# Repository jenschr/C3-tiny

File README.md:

# ESP32 C3-tiny
A Tiny but very functional DevBoard with Temperature/Moisture sensor and 5 programmable LEDs.

## Why smaller?

The official devboard from Espressif is crazy big for such a tiny module? I wanted to make something that leaves two rows on each side when put into a normal half-size breadboard, while testing out the Espressif ESP32 C3 module. Also - I could make this as a christmas gift for my son since he studies electronics and likes RiscV? And then I could publish it as a starting point for others to design their own boards? Why not!

I won't say that the pinout isn't a bit messy (as not in correct order), but all pins are broken out and this project should make it easy for anyone to create their own Espressif C3 based boards. The repository is complete with [Kicad files](pcb/), [BOM](bom/) and [test code for Arduino](code/).

## Pinout

[*] All the module pins are broken out and some pins such as pin 18 + 19 is used for the USB connection. That means that you cannot connect anything to these if you want to use USB.

[*] You also cannot use pins 6 (SDA) and 7 (SCL) for other things if you want to also use the SHT31 sensor connected to these pins (I2C Bus). Other I2C devices shopuld also be connected to these pins. Note that there are pullup resistors on these pins. If you keep this in mind, you can use the pins if you don't use I2C.

[*] The Boot button may be used as an input - after startup has finished.

## Arduino usage

Select "ESP32C3 Dev Module" as the board and set "USB CDC on Boot" to true. The SHT31 sensor is on address 0x44 and you need to start I2C using pins 6 and 7 like this:

`Wire.begin(6,7);`

The five RGB LEDs are connected to pin 8. Check out the code example for details.

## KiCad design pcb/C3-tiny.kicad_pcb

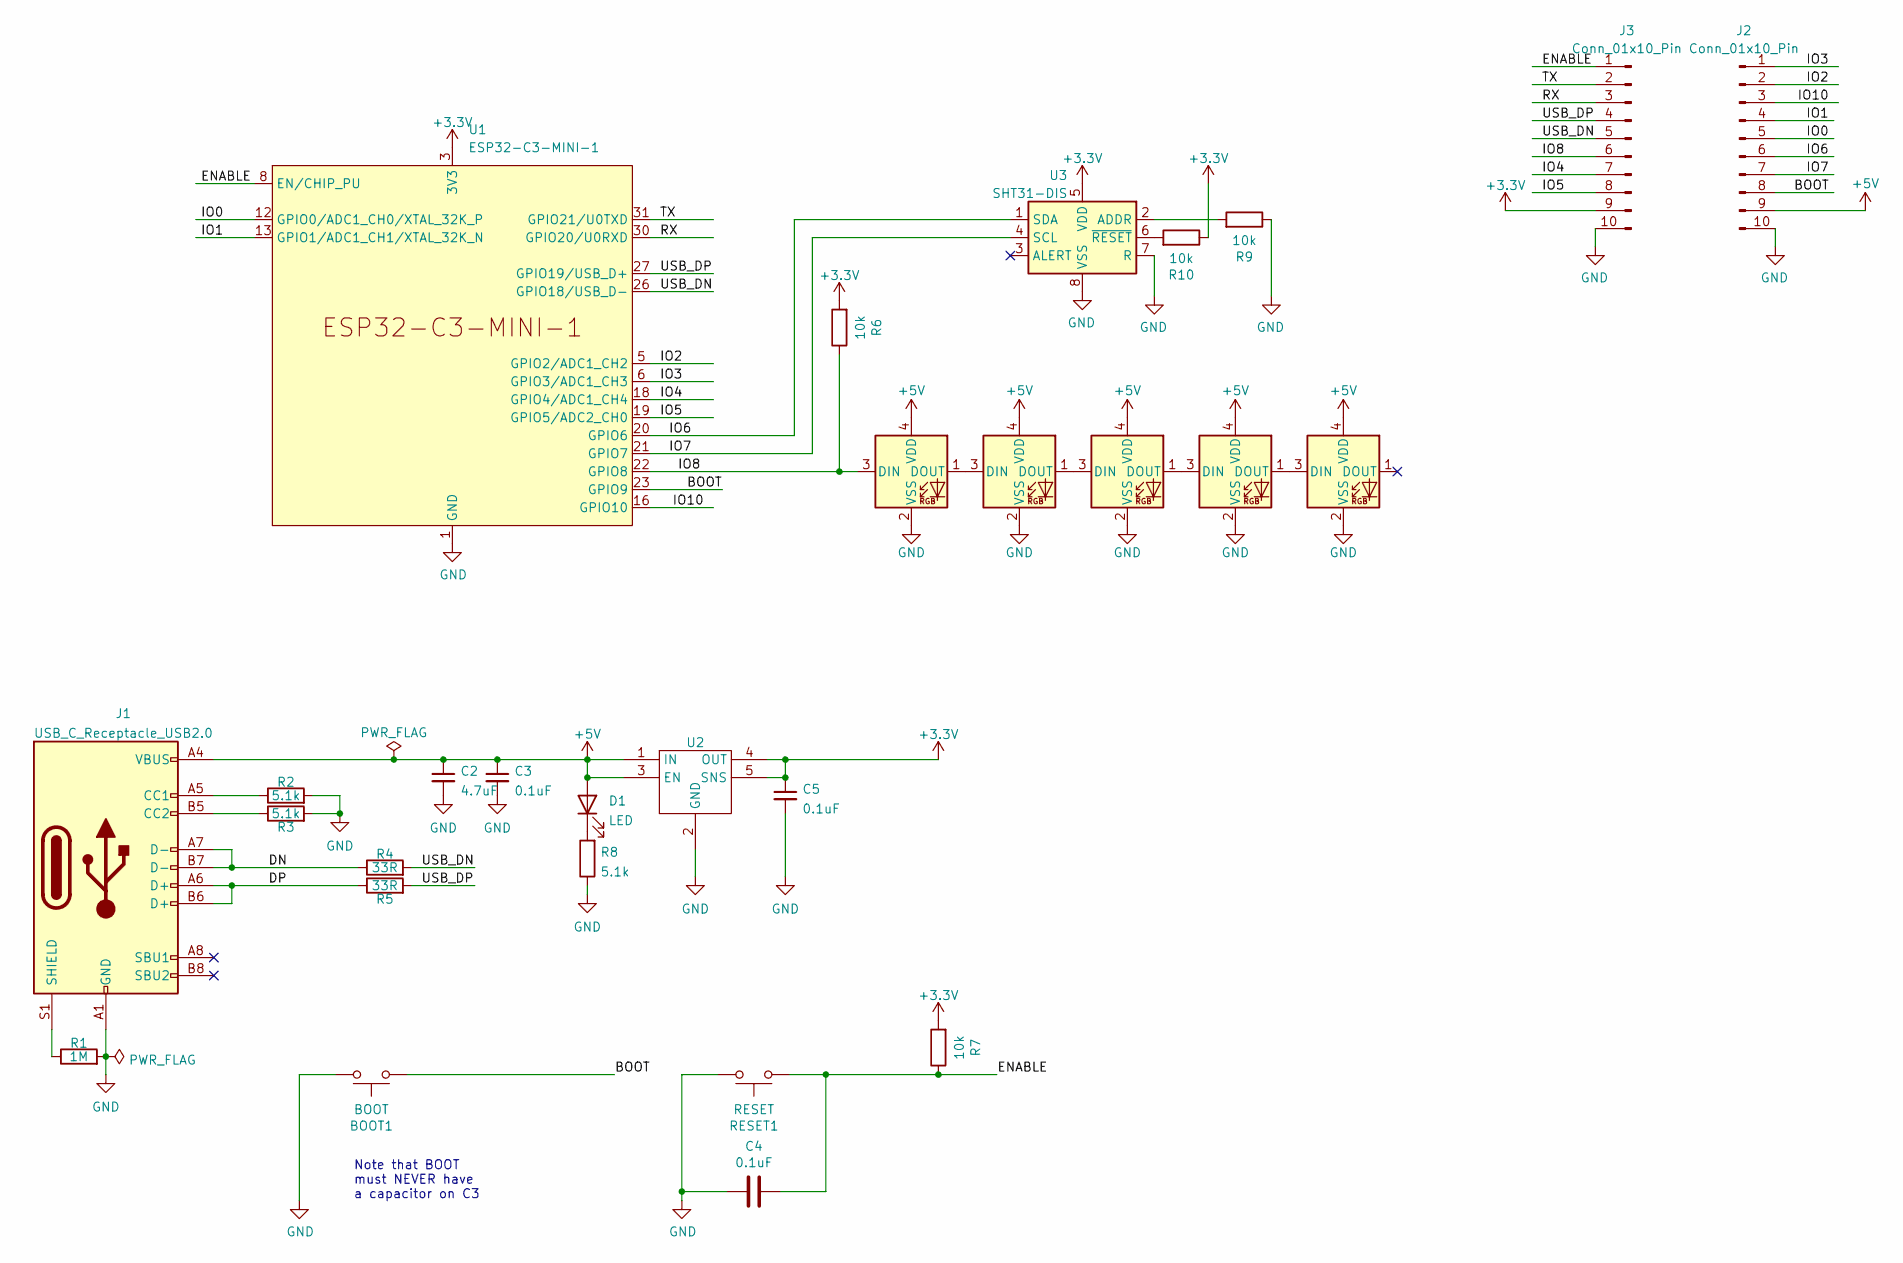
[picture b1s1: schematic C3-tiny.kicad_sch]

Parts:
BOOT1: BOOT; KMR241GLFS; MPN KMR241GLFS
C2: 4.7uF; C_0805_2012Metric
C3, C4, C5: 0.1uF; C_0603_1608Metric_Pad1.08x0.95mm_HandSolder
D1: LED; LED_0603_1608Metric_Pad1.05x0.95mm_HandSolder
J1: USB_C_Receptacle_USB2.0; TYPE-C-31-M-14
J2, J3: Conn_01x10_Pin; PinHeader_1x10_P2.54mm_Vertical
L1, L2, L3, L4, L5: SK6812MINI; LED_SK6812_EC15_1.5x1.5mm
R1: 1M; R_0603_1608Metric_Pad0.98x0.95mm_HandSolder
R2, R3, R8: 5.1k; R_0603_1608Metric
R4, R5: 33R; R_0603_1608Metric
R6, R7, R9, R10: 10k; R_0603_1608Metric; MPN RMCF0603JG10K0
RESET1: RESET; KMR241GLFS; MPN KMR241GLFS
U1: ESP32-C3-MINI-1
U2: NCP692MN33T2G; DFN-6-1EP_3x3mm_P0.95mm_EP1.7x2.6mm
U3: SHT31-DIS; Sensirion_DFN-8-1EP_2.5x2.5mm_P0.5mm_EP1.1x1.7mm; MPN SHT31-DIS

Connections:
+3.3V: C5.1, J3.9, R6.2, R7.2, R10.1, U1.3 (3V3), U2.4 (OUT), U2.5 (SNS), U3.5 (VDD)
+5V: C2.1, C3.1, D1.2 (A), J1.A4 (VBUS), J1.A9 (VBUS), J1.B4 (VBUS), J1.B9 (VBUS), J2.9, L1.4 (VDD), L2.4 (VDD), L3.4 (VDD), L4.4 (VDD), L5.4 (VDD), U2.1 (IN), U2.3 (EN), U2.6 (IN)
/BOOT: BOOT1.1, J2.8, U1.23 (GPIO9)
/DN: J1.A7 (D-), J1.B7 (D-), R4.1
/DP: J1.A6 (D+), J1.B6 (D+), R5.1
/ENABLE: C4.1, J3.1, R7.1, RESET1.1, U1.8 (EN/CHIP_PU)
/IO0: J2.5, U1.12 (GPIO0/ADC1_CH0/XTAL_32K_P)
/IO1: J2.4, U1.13 (GPIO1/ADC1_CH1/XTAL_32K_N)
/IO2: J2.2, U1.5 (GPIO2/ADC1_CH2)
/IO3: J2.1, U1.6 (GPIO3/ADC1_CH3)
/IO4: J3.7, U1.18 (GPIO4/ADC1_CH4)
/IO5: J3.8, U1.19 (GPIO5/ADC2_CH0)
/IO6: J2.6, U1.20 (GPIO6), U3.1 (SDA)
/IO7: J2.7, U1.21 (GPIO7), U3.4 (SCL)
/IO8: J3.6, L1.3 (DIN), R6.1, U1.22 (GPIO8)
/IO10: J2.3, U1.16 (GPIO10)
/RX: J3.3, U1.30 (GPIO20/U0RXD)
/TX: J3.2, U1.31 (GPIO21/U0TXD)
/USB_DN: J3.5, R4.2, U1.26 (GPIO18/USB_D-)
/USB_DP: J3.4, R5.2, U1.27 (GPIO19/USB_D+)
GND: BOOT1.2, C2.2, C3.2, C4.2, C5.2, J1.A1 (GND), J1.A12 (GND), J1.B1 (GND), J1.B12 (GND), J2.10, J3.10, L1.2 (VSS), L2.2 (VSS), L3.2 (VSS), L4.2 (VSS), L5.2 (VSS), R1.2, R2.2, R3.2, R8.1, R9.1, RESET1.2, U1.1 (GND), U1.2 (GND), U1.11 (GND), U1.14 (GND), U1.36 (GND), U1.37 (GND), U1.38 (GND), U1.39 (GND), U1.40 (GND), U1.41 (GND), U1.42 (GND), U1.43 (GND), U1.44 (GND), U1.45 (GND), U1.46 (GND), U1.47 (GND), U1.48 (GND), U1.49 (GND), U1.50 (GND), U1.51 (GND), U1.52 (GND), U1.53 (GND), U2.2 (GND), U2.7 (GND), U3.7 (R), U3.8 (VSS), U3.9 (VSS)
unnamed: D1.1 (K), R8.2
unnamed: J1.A5 (CC1), R2.1
unnamed: J1.B5 (CC2), R3.1
unnamed: J1.S1 (SHIELD), R1.1
unnamed: L1.1 (DOUT), L2.3 (DIN)
unnamed: L2.1 (DOUT), L3.3 (DIN)
unnamed: L3.1 (DOUT), L4.3 (DIN)
unnamed: L4.1 (DOUT), L5.3 (DIN)
unnamed: R9.2, U3.2 (ADDR)
unnamed: R10.2, U3.6 (~RESET)

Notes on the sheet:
Note that BOOT must NEVER have a capacitor on C3

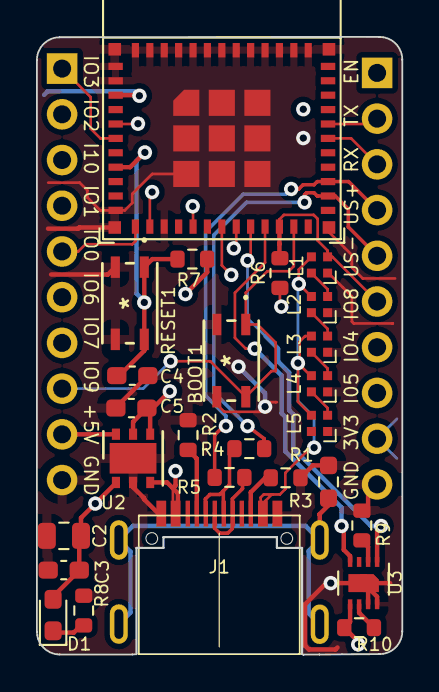
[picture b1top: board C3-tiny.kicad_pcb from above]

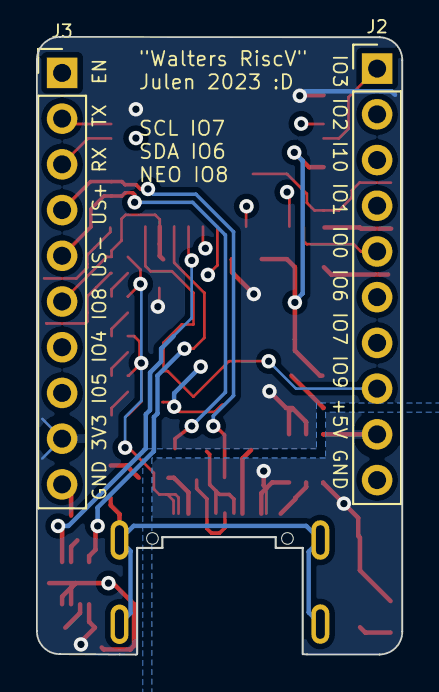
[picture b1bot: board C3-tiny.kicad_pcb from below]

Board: 4 copper layers, 20.3 x 34.3 mm, 28 parts (2 on the bottom side), 31 nets.

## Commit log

2024-01-05 First public version after testing
2024-01-05 Pinout description added
2024-01-05 text
2024-10-04 Removed cap on BOOT. Cleanup some minor errors

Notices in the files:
parts and their libraries:
Copyright 2016 Accelerated Designs. All rights reserved.
